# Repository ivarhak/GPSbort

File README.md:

Hello reader!

This project was made as part of the Hack Club Macondo hardware event. 
The main idea was that I wanted to familiarize myself with design of RF related applications on PCBs.

The board has the following central components: 
NEO-N9M GPS module 
USB Type-C connector 
MT3608 Boost converter 
ESP32-C3-WROOM 
2 SMA jacks for antennas (LORA and GPS) 
AMS1117-3.3 LDO 
DL-RFM95 LORA transceiver

These components allow the board to recieve its GPS position, do some computation then transmit using built in wifi or bluetooth or even using LORA signal up to 5km!
Useful in scenarios like a missing hiker who needs to tell others where they are, or if you have a rocket thats drifted out of your predicted landing zone and you need to find it.

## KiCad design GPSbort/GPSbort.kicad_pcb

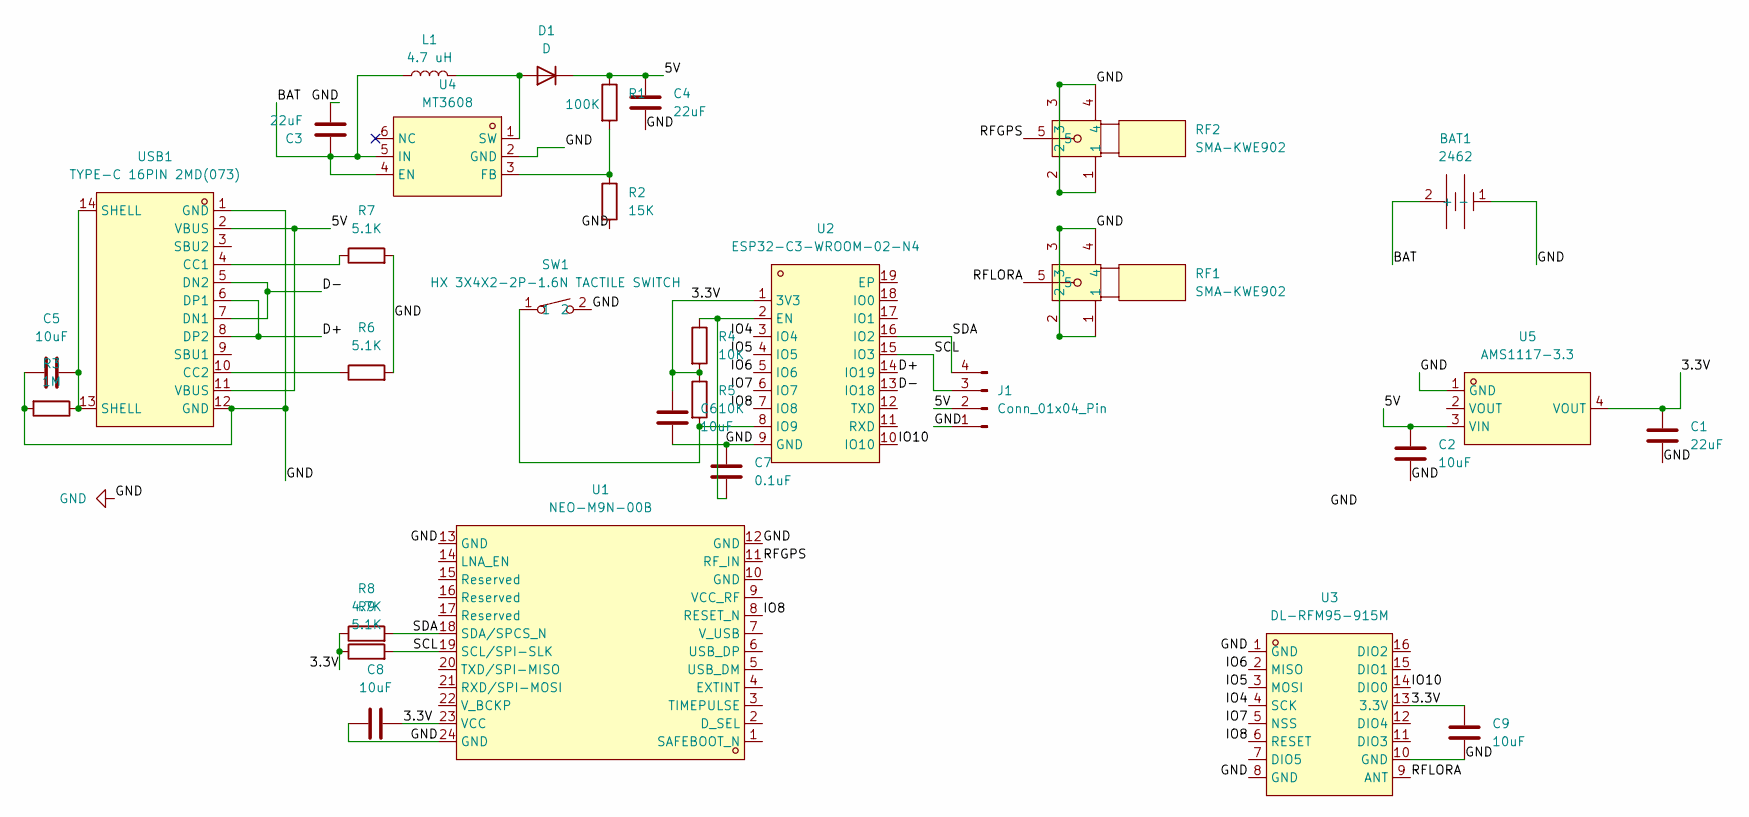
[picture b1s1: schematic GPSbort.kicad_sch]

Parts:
BAT1: 2462; BAT-TH_2P-P14.50_2462; MPN 2462; LCSC Part C3029547
C1, C3, C4: 22uF; C_1206_3216Metric
C2, C5, C6, C8, C9: 10uF; C_1206_3216Metric
C7: 0.1uF; C_1206_3216Metric
D1: D; D_1206_3216Metric
J1: Conn_01x04_Pin; PinHeader_1x04_P2.54mm_Vertical
L1: 4.7 uH; L_1206_3216Metric
R1: 100K; R_1206_3216Metric
R2: 15K; R_1206_3216Metric
R3: 1M; R_1206_3216Metric
R4, R5: 10K; R_1206_3216Metric
R6, R7, R9: 5.1K; R_1206_3216Metric
R8: 4.7K; R_1206_3216Metric
RF1, RF2: SMA-KWE902; SMA-TH_SMA-KWE902; LCSC Part C914554
SW1: HX 3X4X2-2P-1.6N TACTILE SWITCH; KEY-SMD_L4.0-W3.0-LS4.9-1; LCSC Part C49234124
U1: NEO-M9N-00B; GPSM-SMD_24P-L16.0-W12.2-P1.10-BL; MPN NEO-M9N-00B; LCSC Part C5119087
U2: ESP32-C3-WROOM-02-N4; BULETM-SMD_ESPRESSIF_ESP32-C3-WROOM-02-N4-4MB; MPN ESP32-C3-WROOM-02-N4; LCSC Part C2934560
U3: DL-RFM95-915M; LCC-16_L16.0-W16.0-P2.00-TL; MPN DL-RFM95-915M; LCSC Part C2844473
U4: MT3608; SOT-23-6_L2.9-W1.6-P0.95-LS2.8-BL; MPN MT3608; LCSC Part C84817
U5: AMS1117-3.3; SOT-223-3_L6.5-W3.4-P2.30-LS7.0-BR; MPN AMS1117-3.3; LCSC Part C6186
USB1: TYPE-C 16PIN 2MD(073); USB-C-SMD_TYPE-C-6PIN-2MD-073; LCSC Part C2765186

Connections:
/3.3V: C1.1, C6.1, C8.1, C9.1, R4.2, R5.1, R8.1, R9.1, U1.23 (VCC), U2.1 (3V3), U3.13 (3.3V), U5.4 (VOUT)
/5V: C2.1, C4.1, D1.1 (K), J1.2, R1.1, U5.3 (VIN), USB1.2 (VBUS), USB1.11 (VBUS)
/BAT: BAT1.2 (+), C3.1, L1.1, U4.4 (EN), U4.5 (IN)
/D+: U2.14 (IO19), USB1.6 (DP1), USB1.8 (DP2)
/D-: U2.13 (IO18), USB1.5 (DN2), USB1.7 (DN1)
/IO4: U2.3 (IO4), U3.4 (SCK)
/IO5: U2.4 (IO5), U3.3 (MOSI)
/IO6: U2.5 (IO6), U3.2 (MISO)
/IO7: U2.6 (IO7), U3.5 (NSS)
/IO8: U1.8 (RESET_N), U2.7 (IO8), U3.6 (RESET)
/IO10: U2.10 (IO10), U3.14 (DIO0)
/RFGPS: RF2.5, U1.11 (RF_IN)
/RFLORA: RF1.5, U3.9 (ANT)
/SCL: J1.3, R9.2, U1.19 (SCL/SPI-SLK), U2.15 (IO3)
/SDA: J1.4, R8.2, U1.18 (SDA/SPCS_N), U2.16 (IO2)
GND: BAT1.1 (-), C1.2, C2.2, C3.2, C4.2, C5.1, C6.2, C7.1, C8.2, C9.2, J1.1, R2.2, R3.2, R6.2, R7.2, RF1.1, RF1.2, RF1.3, RF1.4, RF2.1, RF2.2, RF2.3, RF2.4, SW1.2, U1.12 (GND), U1.13 (GND), U1.24 (GND), U2.9 (GND), U3.1 (GND), U3.8 (GND), U3.10 (GND), U4.2 (GND), U5.1 (GND), USB1.1 (GND), USB1.12 (GND)
unnamed: C5.2, R3.1, USB1.13 (SHELL), USB1.14 (SHELL)
unnamed: D1.2 (A), L1.2, U4.1 (SW)
unnamed: C7.2, R4.1, U2.2 (EN)
unnamed: R5.2, SW1.1, U2.8 (IO9)
unnamed: R1.2, R2.1, U4.3 (FB)
unnamed: R7.1, USB1.4 (CC1)
unnamed: R6.1, USB1.10 (CC2)

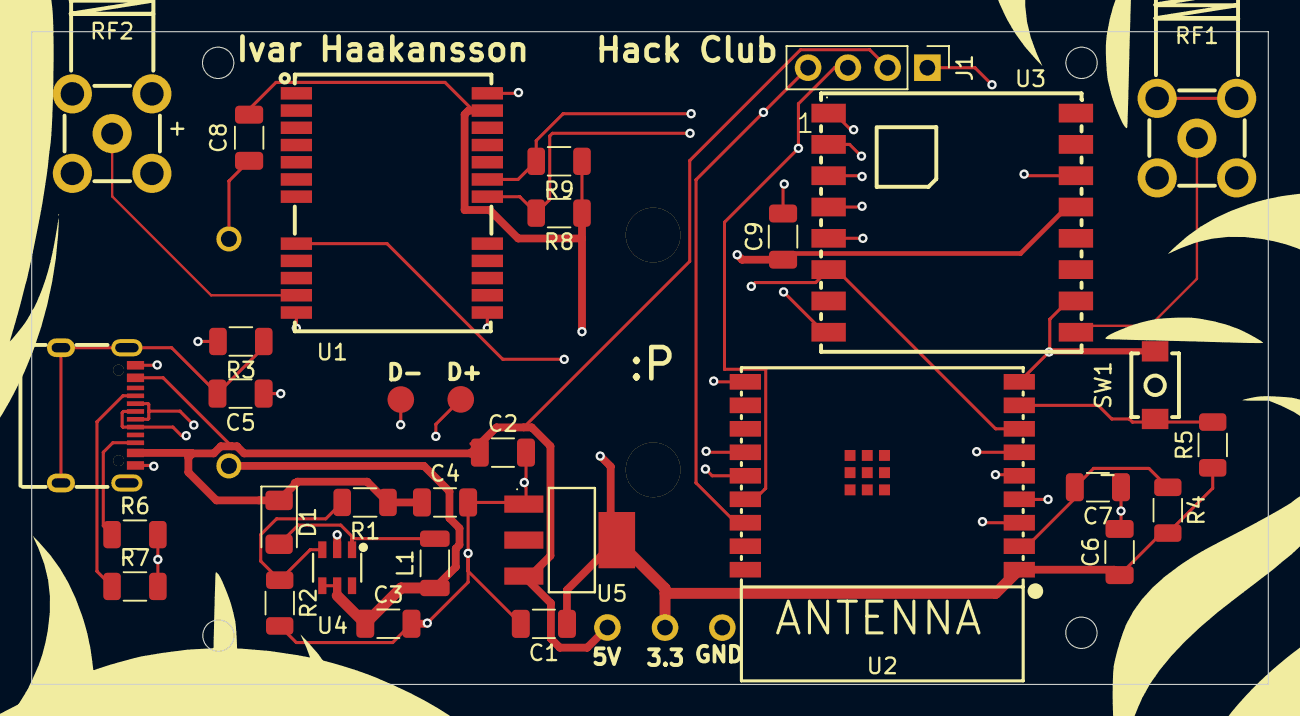
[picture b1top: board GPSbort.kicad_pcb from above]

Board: 4 copper layers, 79.0 x 41.7 mm, 31 parts (1 on the bottom side), 23 nets.

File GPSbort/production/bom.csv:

Designator,Footprint,Quantity,Value,LCSC Part #
"_5, _4, _3, _2, ",,5,,
BAT1,BAT-TH_2P-P14.50_2462,1,2462,C3029547
"C1, C3, C4",1206,3,22uF,
"C2, C5, C6, C8, C9",1206,5,10uF,
C7,1206,1,0.1uF,
D1,1206,1,D,
L1,1206,1,4.7 uH,
R1,1206,1,100K,
R2,1206,1,15K,
R3,1206,1,1M,
"R4, R5",1206,2,10K,
"R6, R7, R9",1206,3,5.1K,
R8,1206,1,4.7K,
"RF1, RF2",SMA-TH_SMA-KWE902,2,SMA-KWE902,C914554
SW1,KEY-SMD_L4.0-W3.0-LS4.9-1,1,HX 3X4X2-2P-1.6N TACTILE SWITCH,C49234124
U1,GPSM-SMD_24P-L16.0-W12.2-P1.10-BL,1,NEO-M9N-00B,C5119087
U2,BULETM-SMD_ESPRESSIF_ESP32-C3-WROOM-02-N4-4MB,1,ESP32-C3-WROOM-02-N4,C2934560
U3,LCC-16_L16.0-W16.0-P2.00-TL,1,DL-RFM95-915M,C2844473
U4,SOT-23-6_L2.9-W1.6-P0.95-LS2.8-BL,1,MT3608,C84817
U5,SOT-223-3_L6.5-W3.4-P2.30-LS7.0-BR,1,AMS1117-3.3,C6186
USB1,USB-C-SMD_TYPE-C-6PIN-2MD-073,1,TYPE-C 16PIN 2MD(073),C2765186
